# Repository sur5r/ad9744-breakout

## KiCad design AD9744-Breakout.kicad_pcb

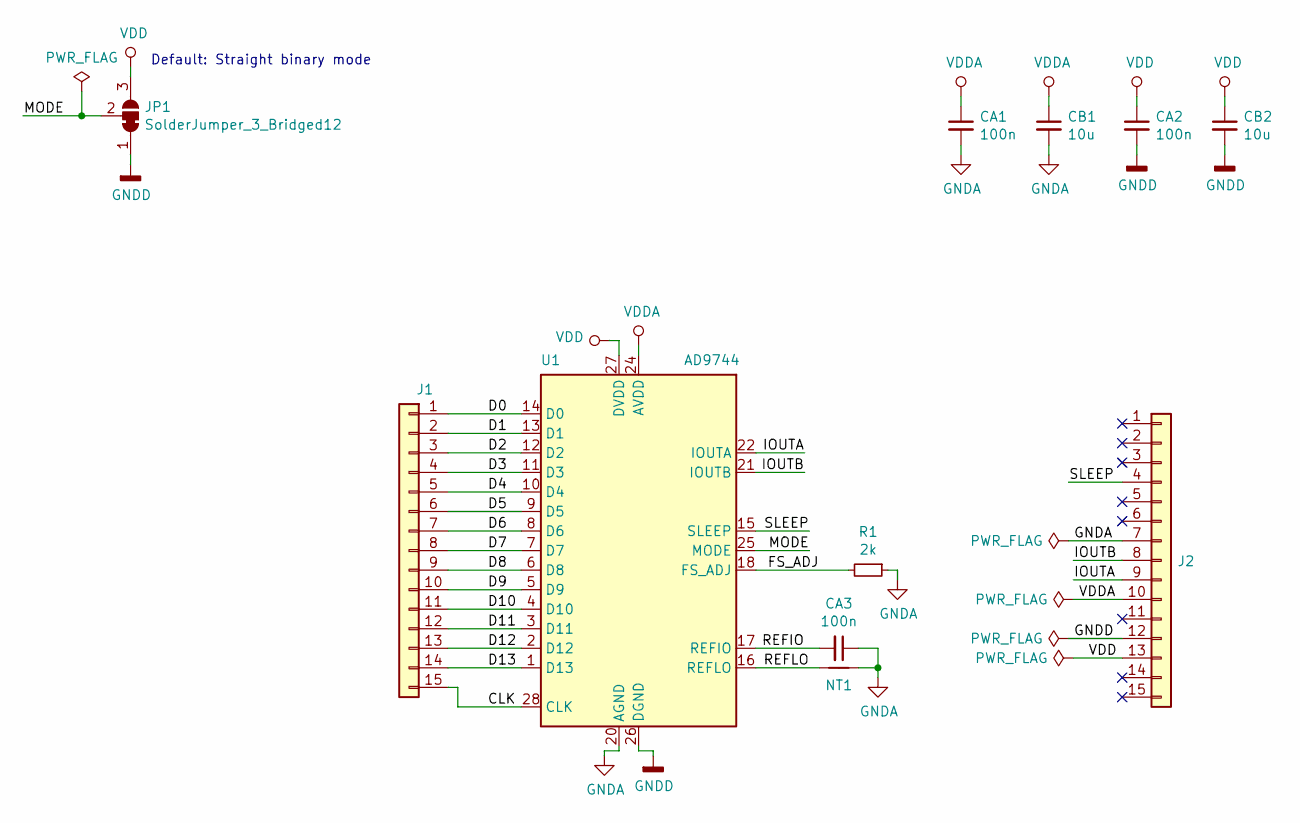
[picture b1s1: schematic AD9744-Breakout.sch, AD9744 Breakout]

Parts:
CA1, CA2, CA3: 100n; C_0603_1608Metric; MPN 06035C104K4T2A
CB1, CB2: 10u; C_1206_3216Metric; MPN UMK316BBJ106KL-T
J1, J2: PinHeader_1x15_P2.54mm_Vertical
JP1: SolderJumper_3_Bridged12; SolderJumper-3_P1.3mm_Bridged12_Pad1.0x1.5mm
NT1: NetTie-2_SMD_Pad0.5mm
R1: 2k; R_0603_1608Metric; MPN ACPP06032K0BE
U1: AD9744; TSSOP-28_4.4x9.7mm_P0.65mm; MPN AD9744ARZ

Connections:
/CLK: J1.15, U1.28 (CLK)
/D0: J1.1, U1.14 (D0)
/D1: J1.2, U1.13 (D1)
/D2: J1.3, U1.12 (D2)
/D3: J1.4, U1.11 (D3)
/D4: J1.5, U1.10 (D4)
/D5: J1.6, U1.9 (D5)
/D6: J1.7, U1.8 (D6)
/D7: J1.8, U1.7 (D7)
/D8: J1.9, U1.6 (D8)
/D9: J1.10, U1.5 (D9)
/D10: J1.11, U1.4 (D10)
/D11: J1.12, U1.3 (D11)
/D12: J1.13, U1.2 (D12)
/D13: J1.14, U1.1 (D13)
/FS_ADJ: R1.2, U1.18 (FS_ADJ)
/IOUTA: J2.9, U1.22 (IOUTA)
/IOUTB: J2.8, U1.21 (IOUTB)
/MODE: JP1.2 (C), U1.25 (MODE)
/REFIO: CA3.2, U1.17 (REFIO)
/REFLO: NT1.1, U1.16 (REFLO)
/SLEEP: J2.4, U1.15 (SLEEP)
GNDA: CA1.2, CA3.1, CB1.2, J2.7, NT1.2, R1.1, U1.20 (AGND)
GNDD: CA2.2, CB2.2, J2.12, JP1.1 (A), U1.26 (DGND)
VDD: CA2.1, CB2.1, J2.13, JP1.3 (B), U1.27 (DVDD)
VDDA: CA1.1, CB1.1, J2.10, U1.24 (AVDD)

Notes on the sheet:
Default: Straight binary mode

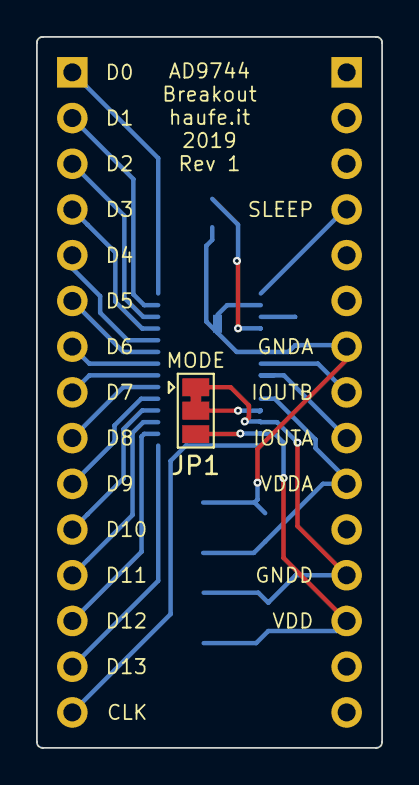
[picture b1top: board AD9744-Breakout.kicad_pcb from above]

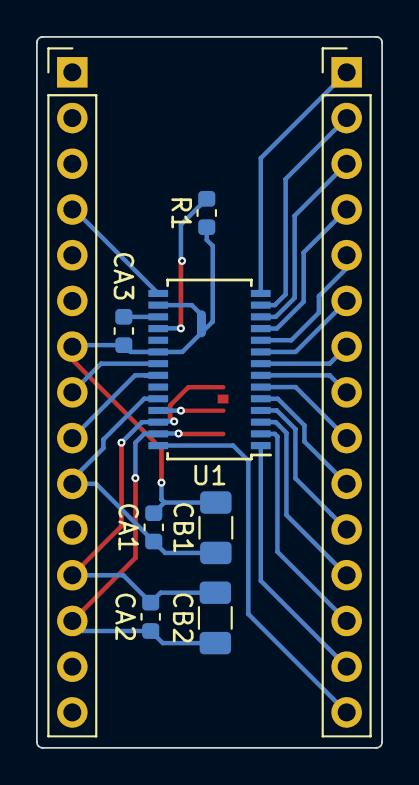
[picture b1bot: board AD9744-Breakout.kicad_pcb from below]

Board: 2 copper layers, 19.2 x 39.5 mm, 11 parts (10 on the bottom side), 26 nets.

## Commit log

2019-08-01 Revision 1
